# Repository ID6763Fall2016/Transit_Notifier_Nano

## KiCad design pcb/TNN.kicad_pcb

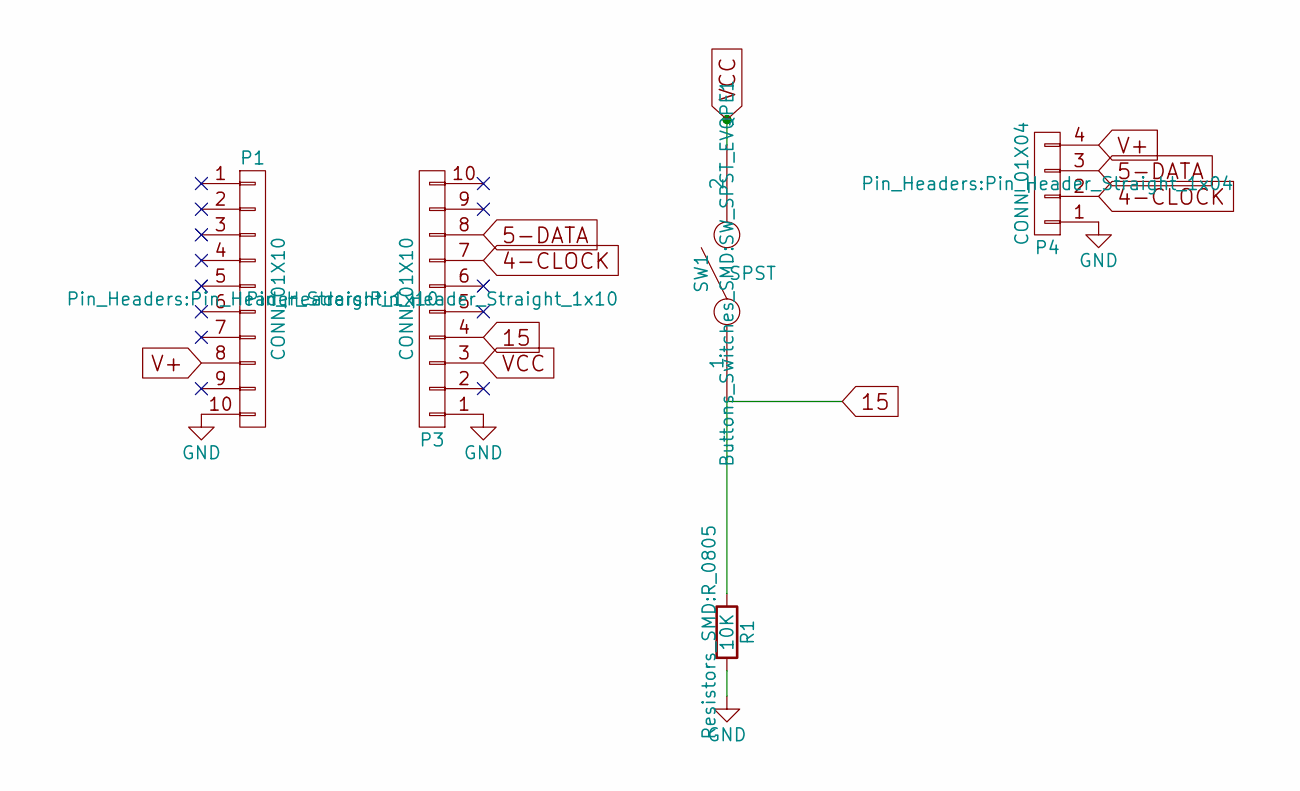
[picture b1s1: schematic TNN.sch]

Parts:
P1, P3: CONN_01X10; Pin_Header_Straight_1x10
P4: CONN_01X04; Pin_Header_Straight_1x04
R1: 10K; R_0805
SW1: SPST; SW_SPST_EVQPE1

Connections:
4-CLOCK: P3.7, P4.2
5-DATA: P3.8, P4.3
15: P3.4, R1.1, SW1.1
GND: P1.10, P3.1, P4.1, R1.2
V+: P1.8, P4.4
VCC: P3.3, SW1.2

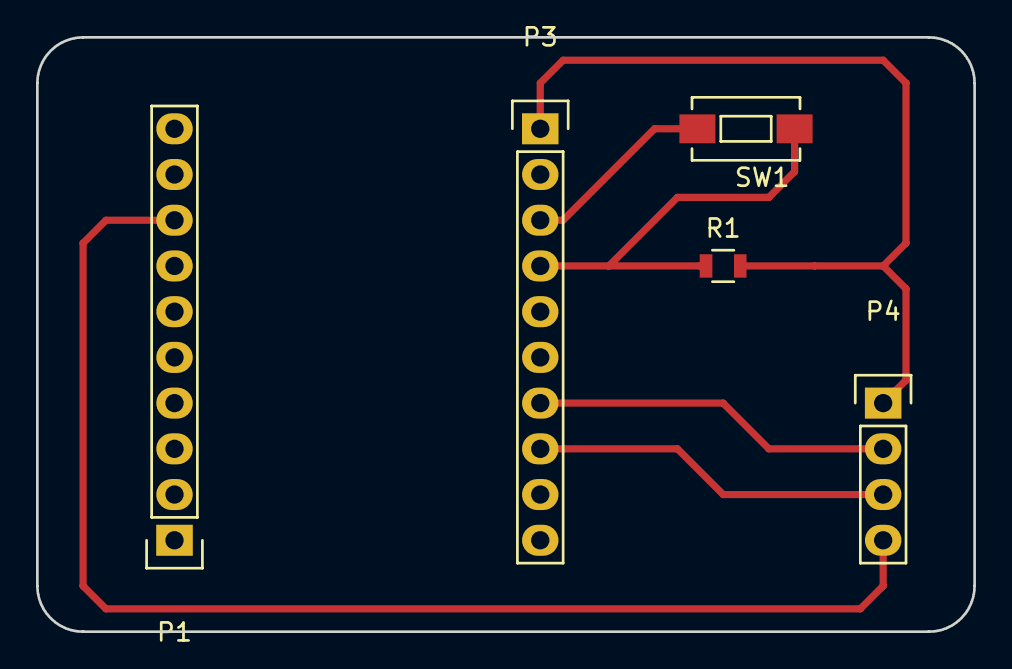
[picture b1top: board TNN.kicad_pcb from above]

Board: 2 copper layers, 52.1 x 33.0 mm, 5 parts (0 on the bottom side), 6 nets.

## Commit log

2016-10-12 adding initial wifi connect code
2016-10-16 [*] Restore dir structure.
2016-10-16 [+] Testing another static html.
2016-10-16 [*] json parsed.
2016-10-16 [+] Mocking server. TODO: simulate browser to next
2016-10-16 [+] Switch to http client.
2016-10-16 [*] Refinement.
2016-10-16 [+] Success in faking browser to trick nextbus new API.
2016-10-17 [+] next bus queries on tech-express and trolley.
2016-10-17 [*] minor mods.
2016-10-17 [+] First attempt with directions API, driving time.
2016-10-17 [+] geo coding for places; [*] move kyes and res.
2016-10-17 [+] Update ahead minutes in the api answer.
2016-10-17 [*] Switch wifi [+] print MAC & ip on http failure
2016-10-17 [+] Update next array. [*] Clearer output.
2016-10-17 [+] walking time and recording
2016-10-18 [x] var name bug. [*] update next bus key.
2016-10-18 [+] compare time.
2016-10-19 [+] Light up different sections.
2016-10-19 [+] debugging json parse issue. worked before.
2016-10-19 [*] inc buffer size. Need future optimization.
2016-10-19 [*] Simplify, time unit min -> sec.
2016-10-19 [*] bus + walk.
2016-10-19 [*] pulsing barely works.
2016-10-19 [+] Simulate crowdedness.
2016-10-19 [*] shift led to right by 2 units; green -> white.
2016-10-20 [*] indentation fix.
2016-10-20 [*] update key logic.
2016-10-20 [+] Multiple google client, just in case.
2016-10-21 [+] Working circuit.
2016-10-21 [*] move left (1x10 head pins) 7*.05 inches.
2016-10-22 [*] Flip over.
2016-10-23 [+] Simulation for presentation.
